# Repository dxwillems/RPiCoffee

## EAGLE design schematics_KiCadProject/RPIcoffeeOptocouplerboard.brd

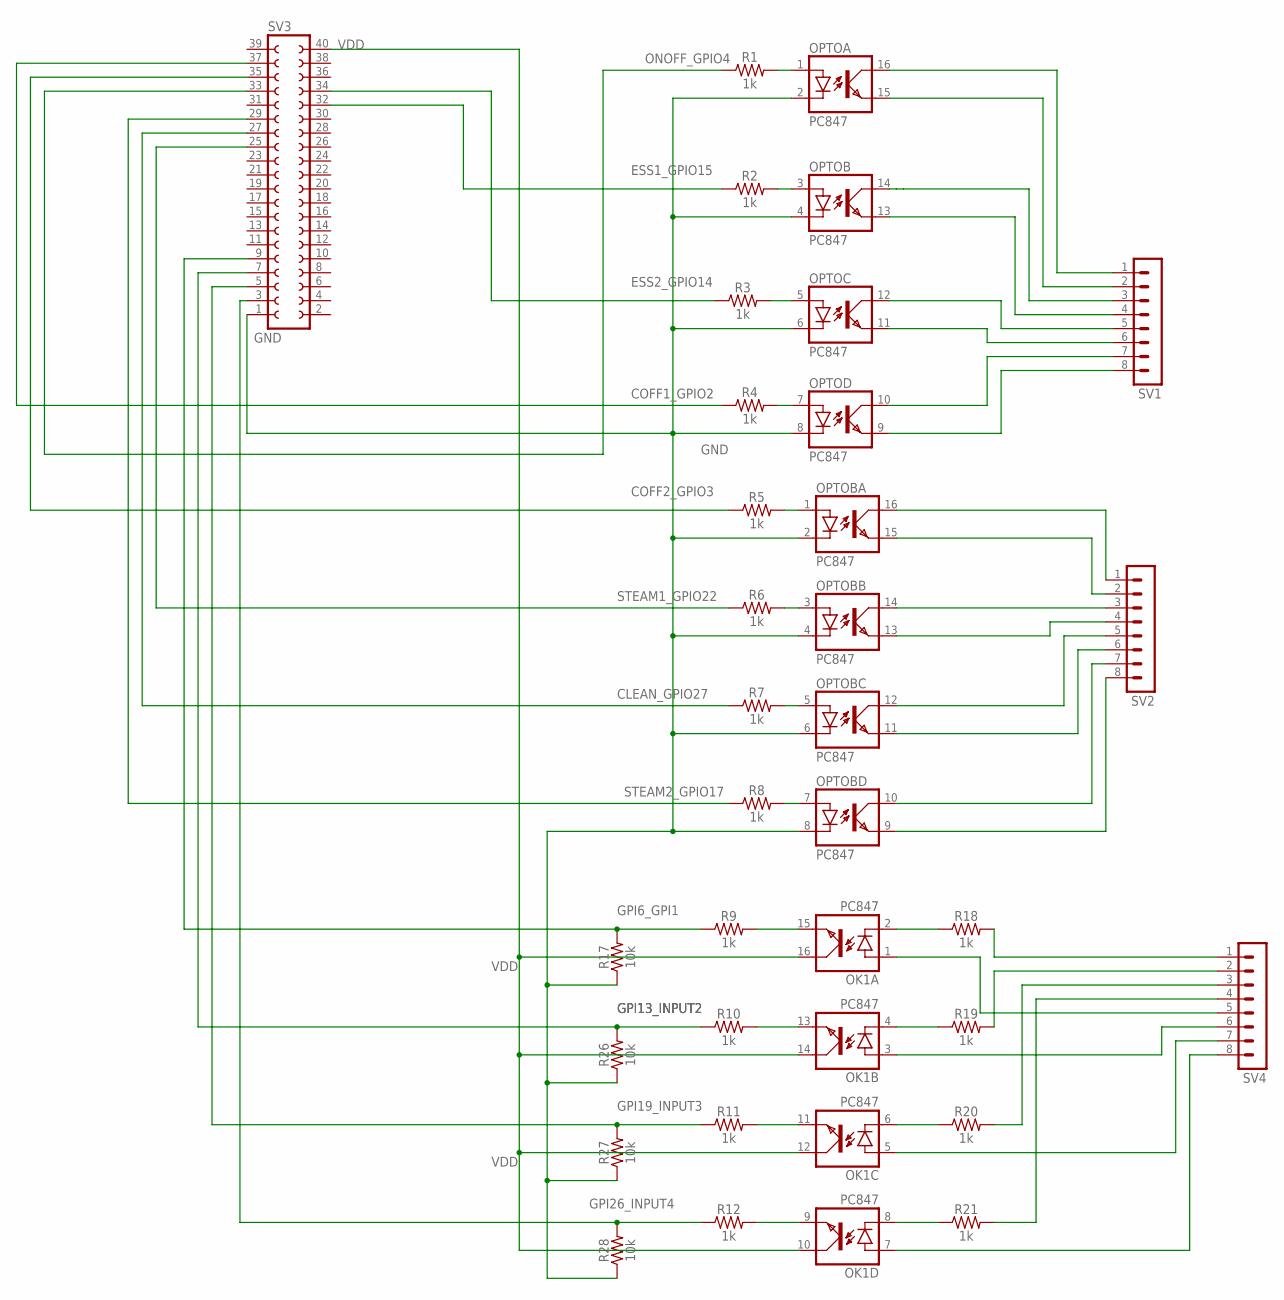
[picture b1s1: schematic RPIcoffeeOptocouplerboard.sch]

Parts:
OK1: PC847; DIL16
OPTO: PC847; DIL16
OPTOB: PC847; DIL16
R1, R2, R3, R4, R5, R6, R7, R8, R9, R10, R11, R12, R18, R19, R20, R21: 1k; AXIAL-0.3
R17, R26, R27, R28: 10k; AXIAL-0.3
SV1, SV2, SV4: MA08-1
SV3: FE20-2

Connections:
CLEAN_GPIO27: R7.P$1 (1), SV3.27
COFF1_GPIO2: R4.P$1 (1), SV3.37
COFF2_GPIO3: R5.P$1 (1), SV3.35
ESS1_GPIO15: R2.P$1 (1), SV3.32
ESS2_GPIO14: R3.P$1 (1), SV3.34
GND: OPTO.2 (C), OPTO.4 (C), OPTO.6 (C), OPTO.8 (C), OPTOB.2 (C), OPTOB.4 (C), OPTOB.6 (C), OPTOB.8 (C), R17.P$1 (1), R26.P$1 (1), R27.P$1 (1), R28.P$1 (1), SV3.1
GPI6_GPI1: R9.P$1 (1), R17.P$2 (2), SV3.9
GPI13_INPUT2: R10.P$1 (1), R26.P$2 (2), SV3.7
GPI19_INPUT3: R11.P$1 (1), R27.P$2 (2), SV3.5
GPI26_INPUT4: R12.P$1 (1), R28.P$2 (2), SV3.3
unnamed: OPTO.16 (COL), SV1.1
unnamed: OPTO.15 (EMIT), SV1.2
unnamed: OPTO.14 (COL), SV1.3
unnamed: OPTO.13 (EMIT), SV1.4
unnamed: OPTO.12 (COL), SV1.5
unnamed: OPTO.11 (EMIT), SV1.6
unnamed: OPTO.10 (COL), SV1.7
unnamed: OPTO.9 (EMIT), SV1.8
unnamed: OPTOB.16 (COL), SV2.1
unnamed: OPTOB.15 (EMIT), SV2.2
unnamed: OPTOB.14 (COL), SV2.3
unnamed: OPTOB.13 (EMIT), SV2.4
unnamed: OPTOB.12 (COL), SV2.5
unnamed: OPTOB.11 (EMIT), SV2.6
unnamed: OPTOB.10 (COL), SV2.7
unnamed: OPTOB.9 (EMIT), SV2.8
unnamed: OK1.2 (C), R18.P$1 (1)
unnamed: OPTOB.7 (A), R8.P$2 (2)
unnamed: OPTOB.5 (A), R7.P$2 (2)
unnamed: OPTOB.3 (A), R6.P$2 (2)
unnamed: OPTOB.1 (A), R5.P$2 (2)
unnamed: OPTO.7 (A), R4.P$2 (2)
unnamed: OPTO.5 (A), R3.P$2 (2)
unnamed: OPTO.1 (A), R1.P$2 (2)
unnamed: OPTO.3 (A), R2.P$2 (2)
unnamed: R18.P$2 (2), SV4.1
unnamed: R19.P$2 (2), SV4.2
unnamed: OK1.4 (C), R19.P$1 (1)
unnamed: R21.P$2 (2), SV4.4
unnamed: OK1.3 (A), SV4.6
unnamed: OK1.6 (C), R20.P$1 (1)
unnamed: OK1.7 (A), SV4.8
unnamed: OK1.5 (A), SV4.7
unnamed: OK1.8 (C), R21.P$1 (1)
unnamed: R20.P$2 (2), SV4.3
unnamed: OK1.1 (A), SV4.5
unnamed: OK1.15 (EMIT), R9.P$2 (2)
unnamed: OK1.13 (EMIT), R10.P$2 (2)
unnamed: OK1.11 (EMIT), R11.P$2 (2)
unnamed: OK1.9 (EMIT), R12.P$2 (2)
ONOFF_GPIO4: R1.P$1 (1), SV3.33
STEAM1_GPIO22: R6.P$1 (1), SV3.25
STEAM2_GPIO17: R8.P$1 (1), SV3.29
VDD: OK1.10 (COL), OK1.12 (COL), OK1.14 (COL), OK1.16 (COL), SV3.40

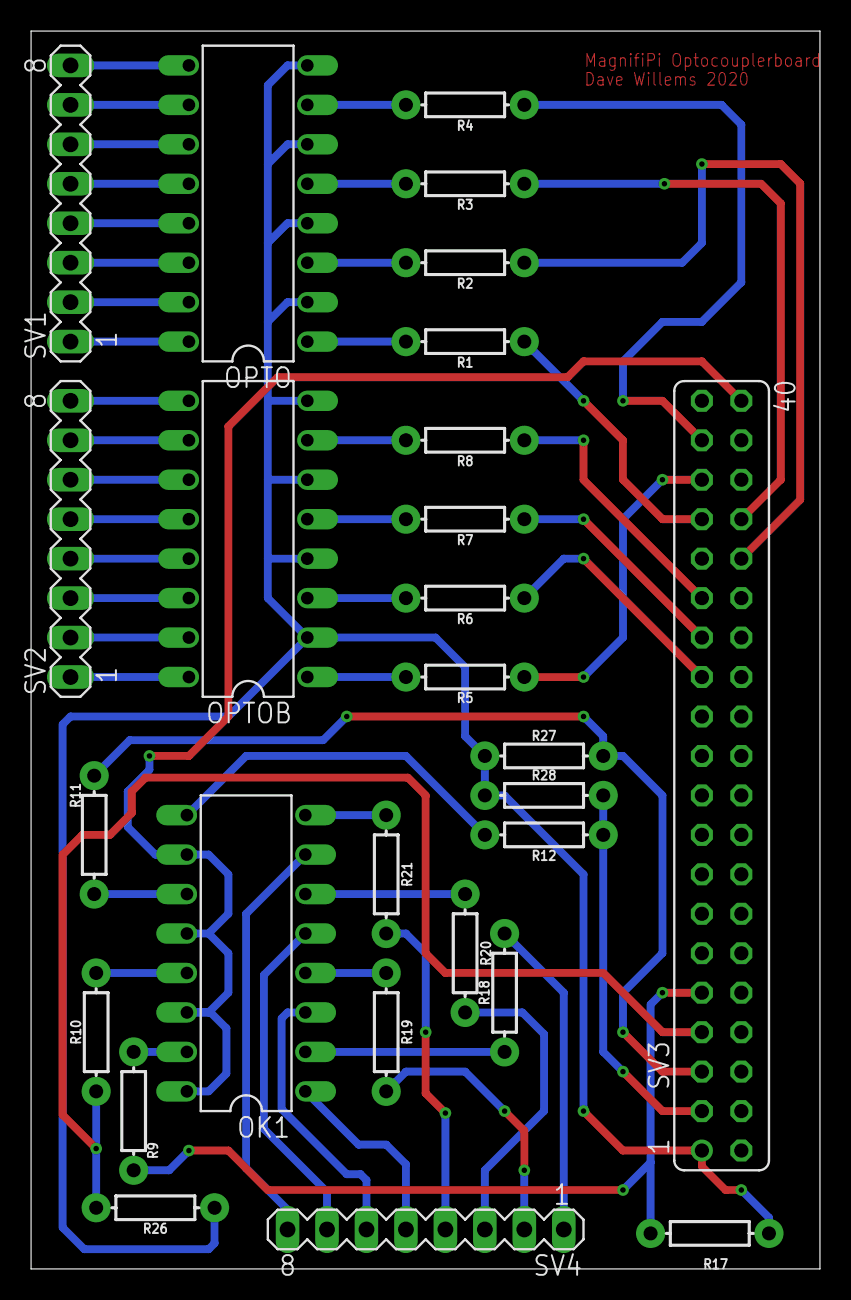
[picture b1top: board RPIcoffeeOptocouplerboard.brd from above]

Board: 2 copper layers, 50.8 x 79.7 mm, 27 parts (0 on the bottom side), 54 nets.

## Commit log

2024-09-15 Add files via upload
    EAGLE files, i made an alternative version of the optocoupler board as i had the pc847 laying around.
    since 2018 our coffee machine is running on this.

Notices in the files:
parts and their libraries:
SparkFun-Resistors: Licensing: Creative Commons ShareAlike 4.0 International - https://creativecommons.org/licenses/by-sa/4.0
